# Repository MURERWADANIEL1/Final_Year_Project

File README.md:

# Respiratory Sound Classification with ESP32 and Deep Learning

This repository contains the complete codebase for a final year project (2024/2025) focused on classifying respiratory diseases from audio sounds. The system uses an ESP32 microcontroller for data acquisition and a Convolutional Neural Network (CNN) for classification.

## Overview

The project's goal is to create a non-invasive diagnostic aid by analyzing respiratory sounds (like coughs or breathing). An ESP32-based hardware device captures audio, streams it wirelessly via Bluetooth Low Energy (BLE) to a computer, where a Python application processes the sound and predicts a potential respiratory condition.

## Key Features

*   **Wireless Data Acquisition**: An ESP32 microcontroller captures audio and streams it in real-time over BLE.
*   **Signal Processing**: Raw audio is converted into mel spectrograms, which are visual representations of the sound spectrum, suitable for image-based deep learning models.
*   **Deep Learning Classification**: A pre-trained TensorFlow/Keras CNN model classifies the spectrogram to identify conditions such as COPD, Pneumonia, Bronchiectasis, and more.
*   **Instant Feedback**: The system provides an immediate prediction with a confidence score.
*   **Visualization**: Generates and displays plots of the audio spectrogram and the model's prediction probabilities for clear interpretation.

## Project Structure
This section details the role of each folder in the repository.

*   **`./` (Root Directory)**
    *   The main project folder containing this `README.md`, `.gitignore`, and other top-level configuration files.

*   **`Project/`**
    *   The primary container for all functional source code, organized into subdirectories for Python application logic, the ML model, and the C++ firmware.

*   **`Project/PythonCode/`**
    *   Contains the Python scripts that form the core of the desktop application.
    *   `RecordingFile.py`: Manages the asynchronous Bluetooth Low Energy (BLE) connection to the ESP32 using the `bleak` and `asyncio` libraries. It discovers the device, connects to the correct service, and streams audio data, saving it as a `.wav` file into the `recordings/` directory.
    *   `Processing_Prediction.py`: Handles the machine learning pipeline. It loads an audio file, preprocesses it into a mel spectrogram, feeds it to the trained model for inference, and visualizes the prediction results.

*   **`Project/Model/`**
    *   Houses the machine learning model assets.
    *   `respiratory_cnn_model.h5`: The final, trained Keras model file. This portable format contains the model's architecture, weights, and training configuration.
    *   `ModelNotebooks/`: Contains Jupyter Notebooks (`.ipynb` files) used for the development and experimentation phase of the model. This is where data exploration, feature engineering, model architecture design, training, and evaluation take place.

*   **`Project/Cpp-Code/`**
    *   Contains the firmware for the ESP32 microcontroller. This C++/Arduino code is responsible for initializing the microphone, sampling audio at the required rate, and transmitting the data wirelessly over BLE.

*   **`recordings/`**
    *   The default output directory for audio files. When `RecordingFile.py` is run, the captured `.wav` audio clip is saved here, ready for processing.

*   **`Predicted_Spectrograms/`**
    *   The default output directory for prediction artifacts. When `Processing_Prediction.py` runs, it saves the generated mel spectrogram image used for the prediction into this folder. This is useful for debugging, analysis, and record-keeping.

*   **`Circuit-Design/`**
    *   Contains all hardware design files. This includes circuit schematics, PCB layouts, and simulation files created in software like Multisim, Proteus, or KiCad.

## System Workflow

1.  **Capture**: The ESP32 device, equipped with a microphone, records respiratory sounds.
2.  **Transmit**: The `RecordingFile.py` script connects to the ESP32 (`ESP32_ML_PROJECT`) and receives the audio stream over BLE, saving it as a `.wav` file in the `recordings/` directory.
3.  **Process & Predict**: The `Processing_Prediction.py` script automatically loads the latest recording.
4.  **Feature Extraction**: It converts the audio into a mel spectrogram.
5.  **Inference**: The spectrogram is fed into the trained CNN model, which outputs a prediction (e.g., "Healthy", "COPD") and a confidence score.
6.  **Visualize**: The results, including the spectrogram and class probabilities, are displayed in a plot. The predicted spectrogram is also saved for review.

## Prerequisites

*   Python 3.8+
*   A computer with Bluetooth support.
*   The custom ESP32 device, programmed with the corresponding firmware and powered on.
*   **Note on `asyncio`**: This project uses `asyncio` for handling BLE communication. It is part of Python's standard library since version 3.4 and does not require a separate installation.
*   Required Python packages. Install them via pip:
    ```bash
    pip install tensorflow numpy librosa opencv-python matplotlib scikit-learn soundfile bleak jupyter
    ```

## How to Use

1.  **Clone the repository:**
    ```bash
    git clone https://github.com/MURERWADANIEL1/Final_Year_Project # Replace with your repo URL if different
    cd Final_Year_Project # Or your repository's root folder name

    ```
2.  **Record Audio**: Power on the ESP32 device. Run the recording script to capture a 15-second audio clip.
    ```bash
    python Project/PythonCode/RecordingFile.py
    ```
3.  **Run Prediction**: Once the recording is saved, run the prediction script. It will automatically find and process the latest audio file.
    ```bash
    python Project/PythonCode/Processing_Prediction.py
    ```
    A window will pop up displaying the diagnostic results and visualizations.

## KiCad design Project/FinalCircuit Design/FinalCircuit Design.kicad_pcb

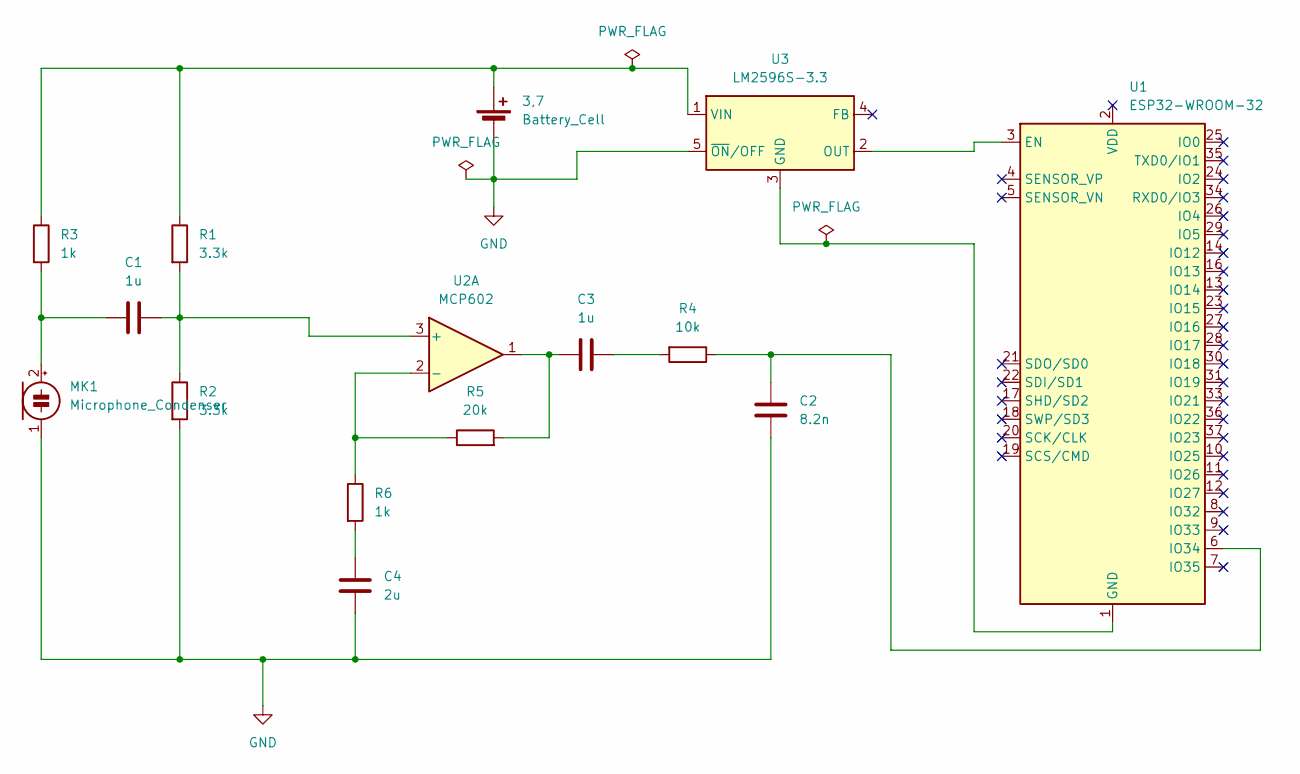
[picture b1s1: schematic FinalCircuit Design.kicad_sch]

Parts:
3,7: Battery_Cell; JST_JWPF_B02B-JWPF-SK-R_1x02_P2.00mm_Vertical
C1, C3: 1u; C_Disc_D3.0mm_W2.0mm_P2.50mm
C2: 8.2n; C_Disc_D3.0mm_W2.0mm_P2.50mm
C4: 2u; C_Disc_D3.0mm_W2.0mm_P2.50mm
MK1: Microphone_Condenser; CUI_CMC-4013-SMT
R1: 3.3k; R_Axial_DIN0309_L9.0mm_D3.2mm_P25.40mm_Horizontal
R2: 3.3k; R_Axial_DIN0309_L9.0mm_D3.2mm_P2.54mm_Vertical
R3, R6: 1k; R_Axial_DIN0309_L9.0mm_D3.2mm_P2.54mm_Vertical
R4: 10k; R_Axial_DIN0309_L9.0mm_D3.2mm_P2.54mm_Vertical
R5: 20k; R_Axial_DIN0309_L9.0mm_D3.2mm_P2.54mm_Vertical
U1: ESP32-WROOM-32
U2: MCP602; SOIC-8_3.9x4.9mm_P1.27mm
U3: LM2596S-3.3; TO-263-5_TabPin3

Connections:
GND: 3,7.2 (-), C2.2, C4.2, MK1.1 (-), R2.2, U3.5 (~ON/OFF)
unnamed: 3,7.1 (+), R1.1, R3.1, U3.1 (VIN)
unnamed: C3.1, R4.2
unnamed: C3.2, R5.2, U2.1
unnamed: C4.1, R6.2
unnamed: C1.2, MK1.2 (+), R3.2
unnamed: U1.3 (EN), U3.2 (OUT)
unnamed: C2.1, R4.1, U1.6 (IO34)
unnamed: C1.1, R1.2, R2.1, U2.3 (+)
unnamed: R5.1, R6.1, U2.2 (-)
unnamed: U1.1 (GND), U1.15 (GND), U1.38 (GND), U1.39 (GND), U3.3 (GND)

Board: 2 copper layers, 15 parts (0 on the bottom side), 11 nets, no tracks yet.

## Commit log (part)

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2025-02-13 Beginning of my code
2025-02-17 Updated Data preprocessing
2025-02-25 Done upto Tuesday 25/02/2025
    Still under development
2025-02-25 Revert "Done upto Tuesday 25/02/2025"
2025-02-27 Completed Preparation stage
    27TH FEB WORKED ON DATA PREPARATION. This stage I segmente audio file by taking every sample and adding crackle and wheezle to each audio. I also encoded the information of wheezle and crackle to the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
2025-03-11 Delete Project/Data_Augmentation
    Was a copy of another
2025-03-11 Add files via upload
    The updated files for the project
2025-03-20 Files
    Update
2025-03-20 Feature extraction
2025-03-20 Removed .wav files from tracking
2025-03-20 Re-added Jupyter notebooks to Git tracking
2025-03-20 Preparation
2025-03-20 Final
2025-03-21 Updated .gitignore and removed unnecessary files
2025-03-21 21st-March-2025
    Started training model
2025-03-22 Saturday 22ND March
    This is the progress, remaining is training
2025-03-22 Update ML_Training.ipynb
    Done Training and Testing
2025-03-23 Bluetooth Transmitter
    I began working on the ability to transmit audio through the Bluetooth Classic (Audio Stream)
2025-03-24 BT and Recording
2025-03-27 My New Progress
2025-03-29 Reconnecting Repo
2025-04-02 My Schematics
2025-04-07 Drawings and Updated code
2025-04-07 7th April
2025-04-10 Circuits
2025-04-10 New Changes
2025-04-12 Updated Circuit
2025-04-15 New Chnages
2025-04-15 16-04-2025 Commit
2025-04-24 23rd April changes
2025-04-25 Software Update
    Completed Software design and implementation. Only work remaining is to adjust the design for accuracy and integration
2025-05-02 Models
2025-05-10 More Update
2025-05-20 Final Commit for the Repo
2025-08-13 Updated Workflow and ReadMe
